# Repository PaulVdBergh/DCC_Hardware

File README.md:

# DCC_Hardware
The repository for DCC Hardware projects

The DCC project is an attempt to implement a DCC (Digital Command Control) Command Station based on the BeagleBone Black platform.
The project consists of four parts:
- DCC_BBB : the Linux code for the BeagleBone.
- DCC_PRU : the PRU code for generating the actuel DCC signal (including RailCom cutout).
- DCC_AVR : the AVR code for additional interfaces (for example Expressnet).
- DCC_Hardware (this repo) : the schematics and PCB-layout files for the hardware (KiCad)

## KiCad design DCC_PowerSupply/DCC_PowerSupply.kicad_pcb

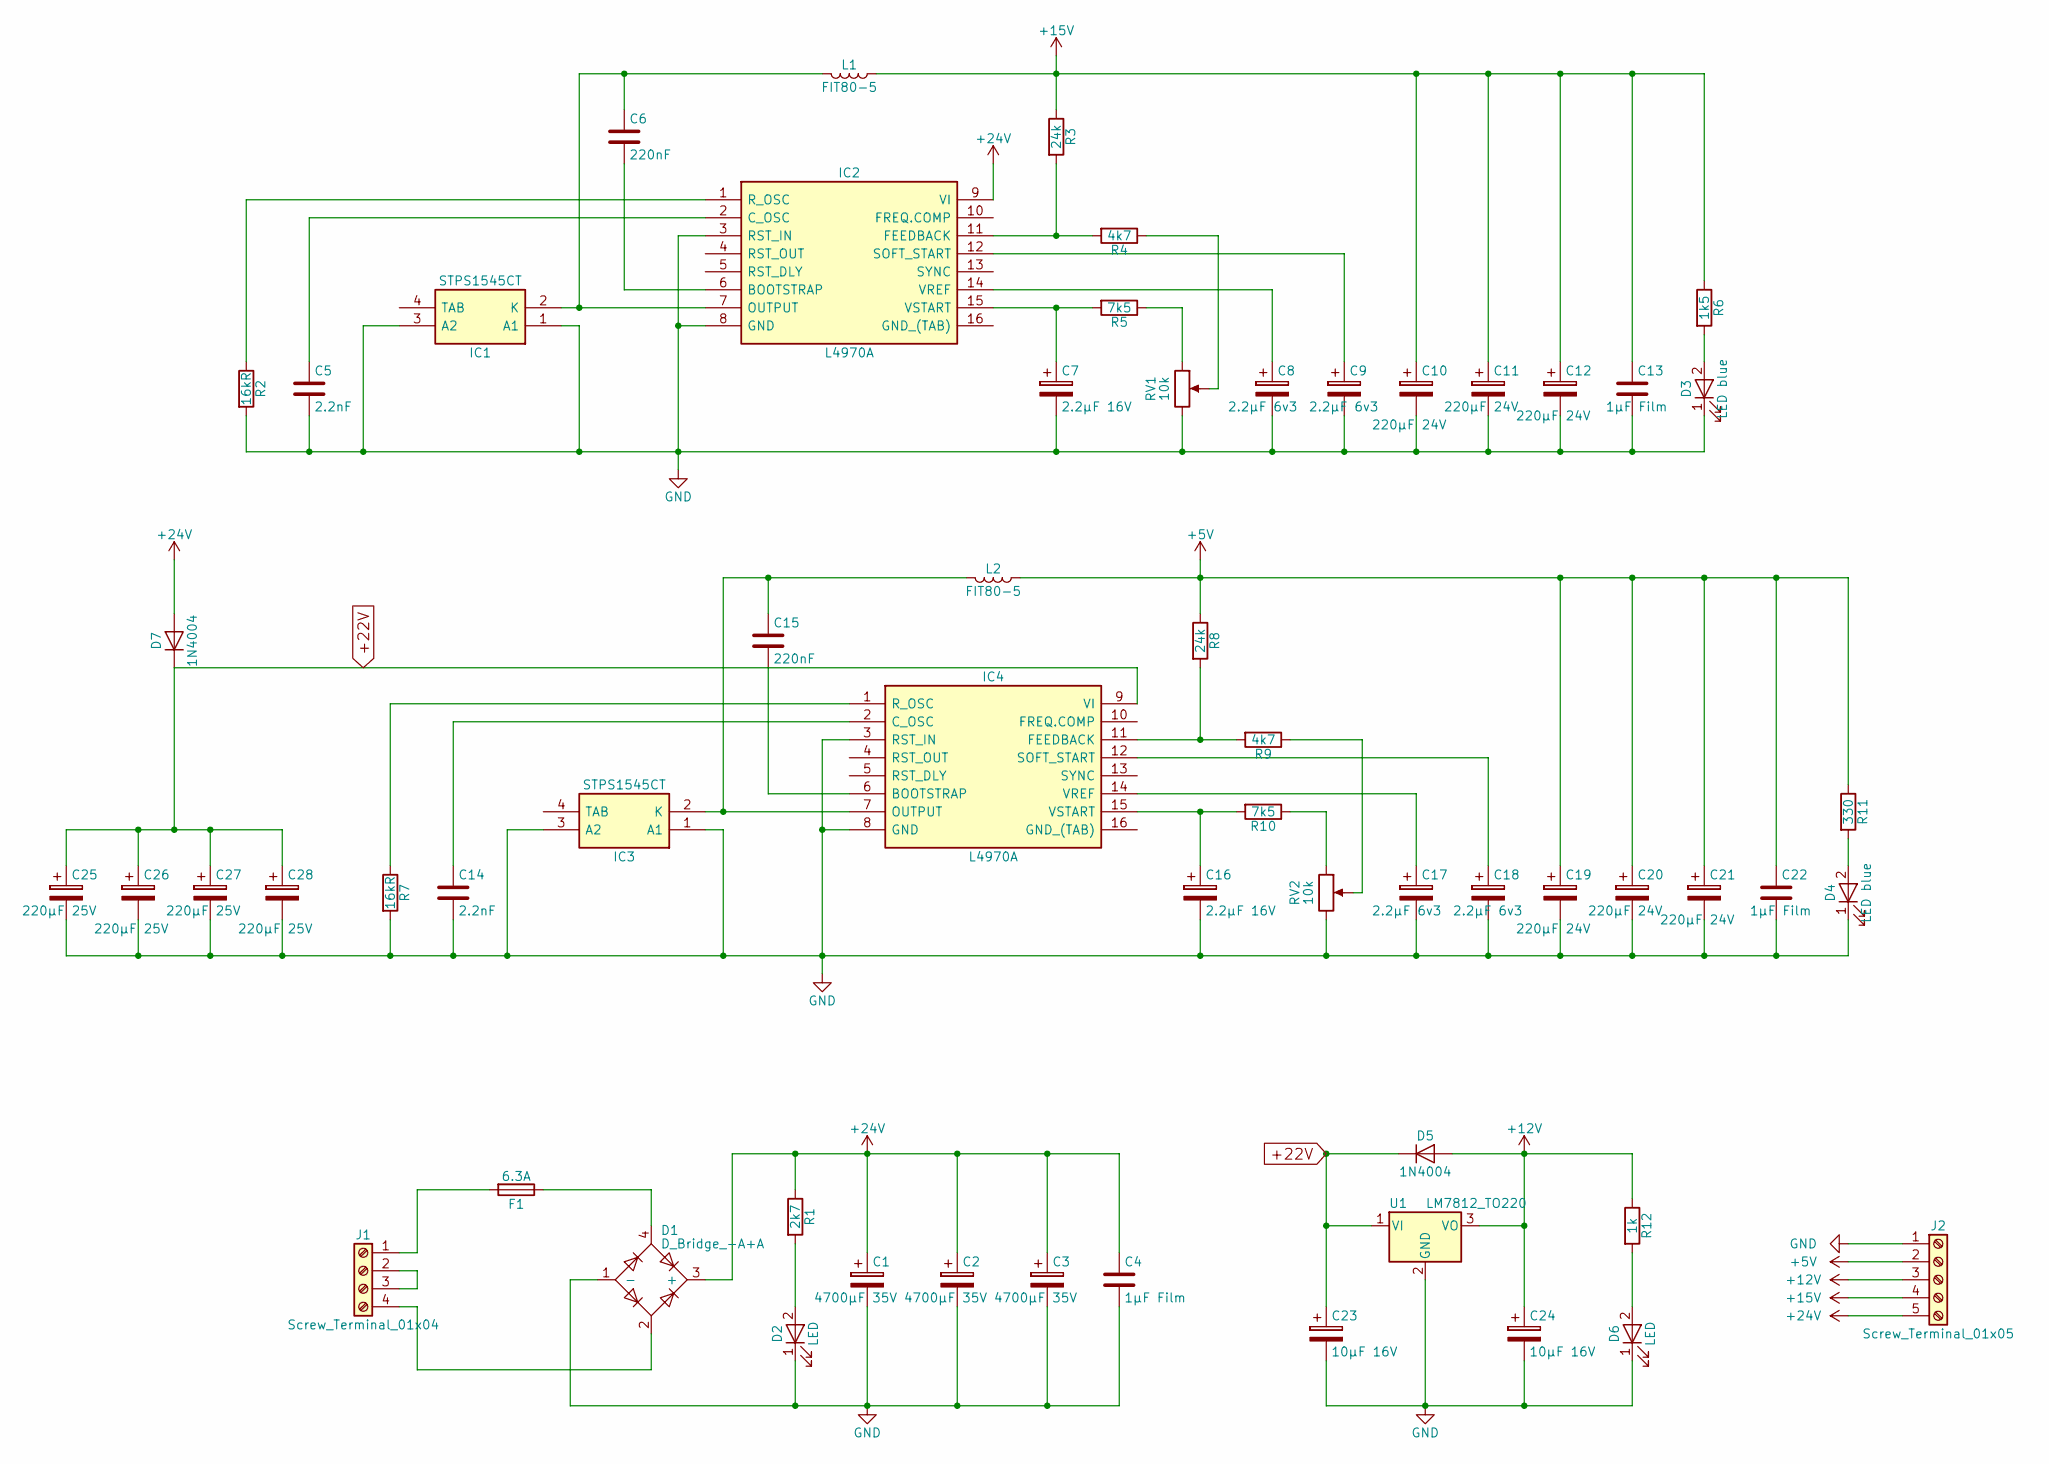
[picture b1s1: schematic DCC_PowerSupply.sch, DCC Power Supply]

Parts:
C1, C2, C3: 4700µF 35V; CP_Radial_D18.0mm_P7.50mm
C4, C13, C22: 1µF Film; C_Rect_L7.2mm_W7.2mm_P5.00mm_FKS2_FKP2_MKS2_MKP2
C5, C14: 2.2nF; C_Rect_L7.2mm_W2.5mm_P5.00mm_FKS2_FKP2_MKS2_MKP2
C6, C15: 220nF; C_Rect_L7.2mm_W2.5mm_P5.00mm_FKS2_FKP2_MKS2_MKP2
C7, C16: 2.2µF 16V; CP_Radial_D5.0mm_P2.00mm
C8, C9, C17, C18: 2.2µF 6v3; CP_Radial_D5.0mm_P2.00mm
C10, C11, C12, C19, C20, C21: 220µF 24V; CP_Radial_D8.0mm_P3.50mm
C23, C24: 10µF 16V; CP_Radial_D5.0mm_P2.00mm
C25, C26, C27, C28: 220µF 25V; CP_Radial_D8.0mm_P3.50mm
D1: D_Bridge_-A+A; Diode_Bridge_15.7x15.7
D2, D6: LED; LED_D3.0mm
D3, D4: LED blue; LED_D3.0mm
D5, D7: 1N4004; D_DO-41_SOD81_P7.62mm_Horizontal
F1: 6.3A; Fuseholder5x20_horiz_SemiClosed_Casing10x25mm
IC1, IC3: STPS1545CT; TO-220_Vertical; Manufacturer_Part_Number STPS1545CT
IC2, IC4: L4970A; Multiwatt-15_Vertical_StaggeredType1; Manufacturer_Part_Number L4970A
J1: Screw_Terminal_01x04; TerminalBlock_Philmore_TB13x_04x5mm_Straight
J2: Screw_Terminal_01x05; TerminalBlock_Philmore_TB13x_05x5mm_Straight
L1, L2: FIT80-5; L_Toroid_Vertical_L28.6mm_W14.3mm_P11.43mm_Bourns_5700
R1: 2k7; R_Axial_DIN0207_L6.3mm_D2.5mm_P10.16mm_Horizontal
R2, R7: 16kR; R_Axial_DIN0207_L6.3mm_D2.5mm_P10.16mm_Horizontal
R3, R8: 24k; R_Axial_DIN0207_L6.3mm_D2.5mm_P10.16mm_Horizontal
R4, R9: 4k7; R_Axial_DIN0207_L6.3mm_D2.5mm_P10.16mm_Horizontal
R5, R10: 7k5; R_Axial_DIN0207_L6.3mm_D2.5mm_P10.16mm_Horizontal
R6: 1k5; R_Axial_DIN0207_L6.3mm_D2.5mm_P10.16mm_Horizontal
R11: 330; R_Axial_DIN0207_L6.3mm_D2.5mm_P10.16mm_Horizontal
R12: 1k; R_Axial_DIN0207_L6.3mm_D2.5mm_P10.16mm_Horizontal
RV1, RV2: 10k; Potentiometer_Trimmer_Bourns_3339P_Horizontal
U1: LM7812_TO220; TO-220_Horizontal

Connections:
+5V: C19.1, C20.1, C21.1, C22.1, J2.2, L2.1, R8.1, R11.1
+12V: C24.1, D5.2 (A), J2.3, R12.1, U1.3 (VO)
+15V: C10.1, C11.1, C12.1, C13.1, J2.4, L1.1, R3.1, R6.1
+22V: C23.1, C25.1, C26.1, C27.1, C28.1, D5.1 (K), D7.1 (K), IC4.9 (VI), U1.1 (VI)
+24V: C1.1, C2.1, C3.1, C4.1, D1.3 (+), D7.2 (A), IC2.9 (VI), J2.5, R1.1
GND: C1.2, C2.2, C3.2, C4.2, C5.2, C7.2, C8.2, C9.2, C10.2, C11.2, C12.2, C13.2, C14.2, C16.2, C17.2, C18.2, C19.2, C20.2, C21.2, C22.2, C23.2, C24.2, C25.2, C26.2, C27.2, C28.2, D1.1 (-), D2.1 (K), D3.1 (K), D4.1 (K), D6.1 (K), IC1.1 (A1), IC1.3 (A2), IC2.3 (RST_IN), IC2.8 (GND), IC3.1 (A1), IC3.3 (A2), IC4.3 (RST_IN), IC4.8 (GND), J2.1, R2.2, R7.2, RV1.3, RV2.3, U1.2 (GND)
unnamed: C5.1, IC2.2 (C_OSC)
unnamed: C6.1, IC1.2 (K), IC2.7 (OUTPUT), L1.2
unnamed: C6.2, IC2.6 (BOOTSTRAP)
unnamed: C7.1, IC2.15 (VSTART), R5.2
unnamed: C8.1, IC2.14 (VREF)
unnamed: C9.1, IC2.12 (SOFT_START)
unnamed: C14.1, IC4.2 (C_OSC)
unnamed: C15.1, IC3.2 (K), IC4.7 (OUTPUT), L2.2
unnamed: C15.2, IC4.6 (BOOTSTRAP)
unnamed: C16.1, IC4.15 (VSTART), R10.2
unnamed: C17.1, IC4.14 (VREF)
unnamed: C18.1, IC4.12 (SOFT_START)
unnamed: D1.2, J1.4
unnamed: D1.4, F1.1
unnamed: D2.2 (A), R1.2
unnamed: D3.2 (A), R6.2
unnamed: D4.2 (A), R11.2
unnamed: D6.2 (A), R12.2
unnamed: F1.2, J1.1
unnamed: IC2.1 (R_OSC), R2.1
unnamed: IC2.11 (FEEDBACK), R3.2, R4.2
unnamed: IC4.1 (R_OSC), R7.1
unnamed: IC4.11 (FEEDBACK), R8.2, R9.2
unnamed: J1.2, J1.3
unnamed: R4.1, RV1.2
unnamed: R5.1, RV1.1
unnamed: R9.1, RV2.2
unnamed: R10.1, RV2.1

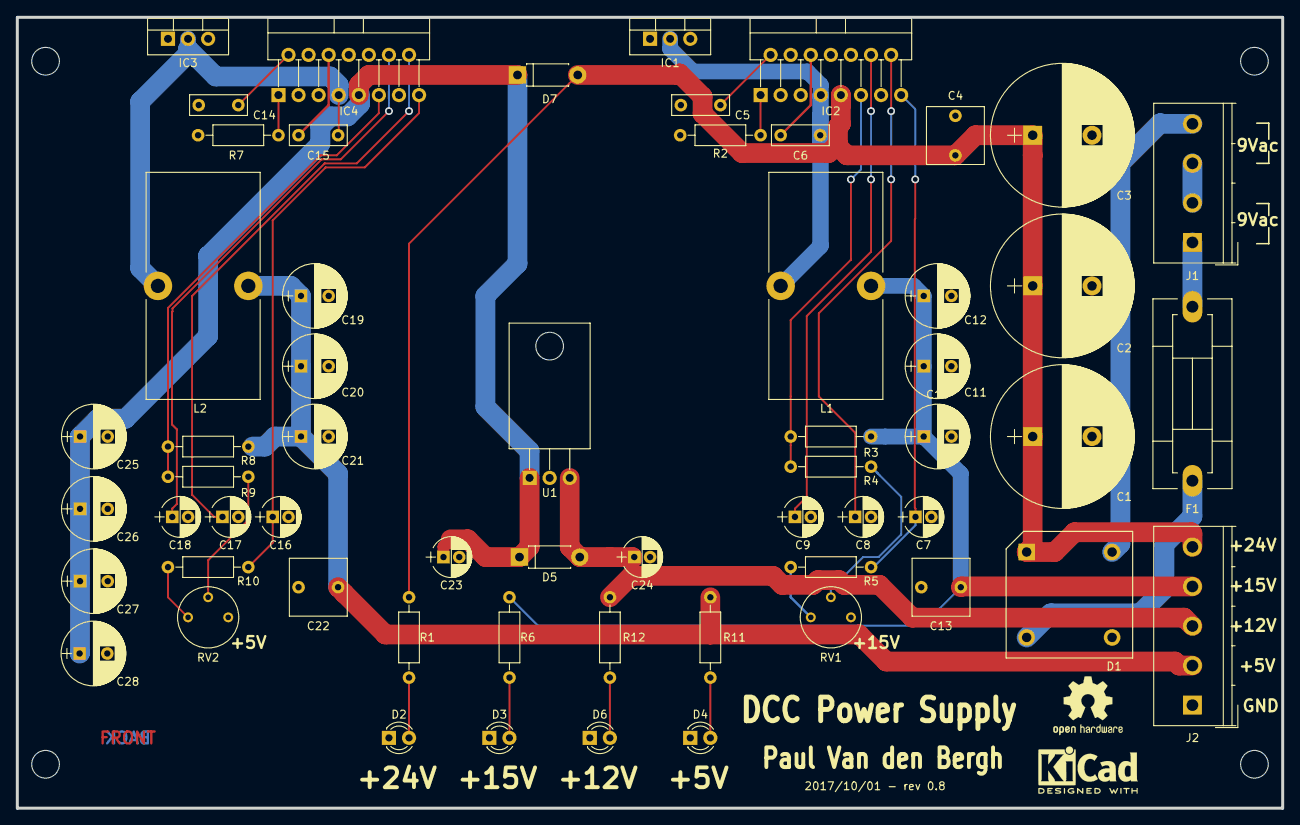
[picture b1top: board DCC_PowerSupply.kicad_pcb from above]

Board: 2 copper layers, 160.0 x 100.0 mm, 60 parts (0 on the bottom side), 34 nets.

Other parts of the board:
2017/10/01 - rev 0.8: EuroBoard160mmX100mm_holes

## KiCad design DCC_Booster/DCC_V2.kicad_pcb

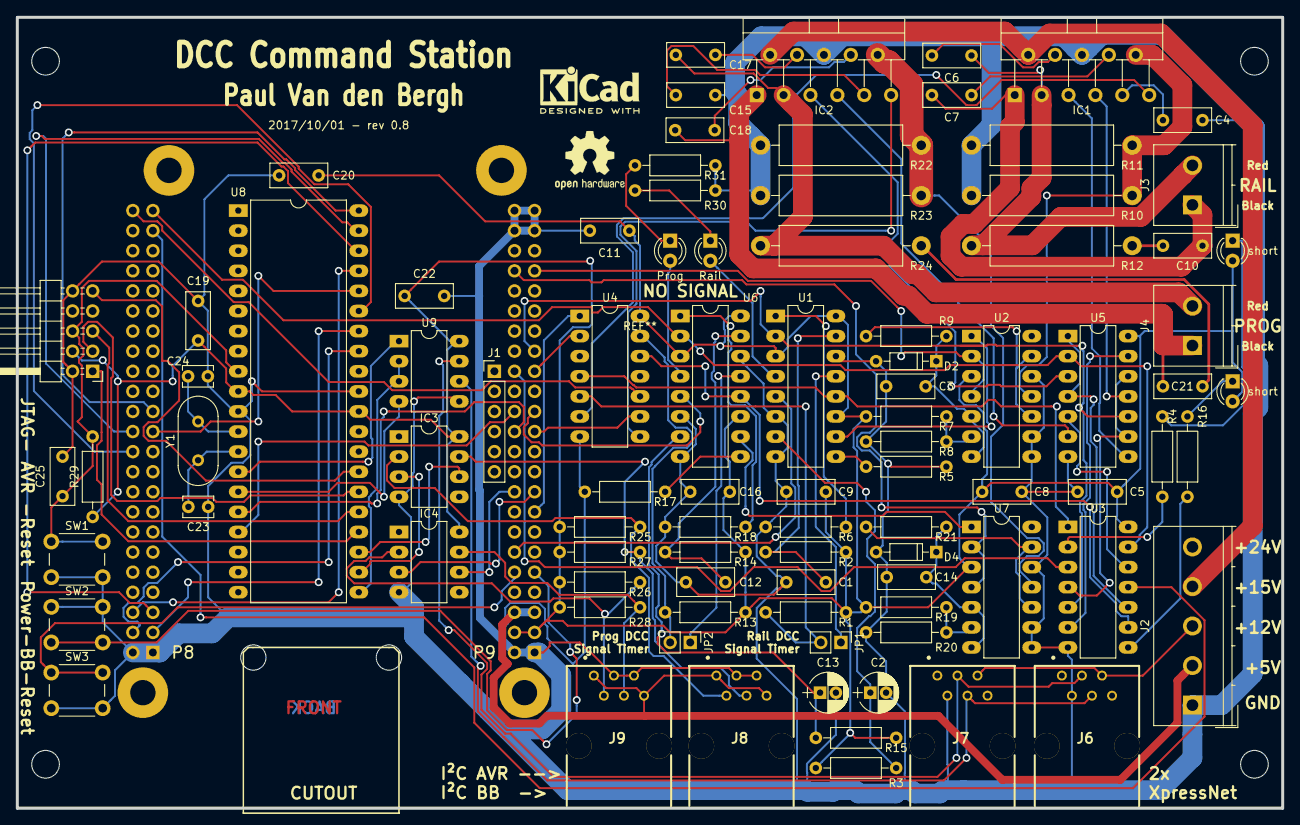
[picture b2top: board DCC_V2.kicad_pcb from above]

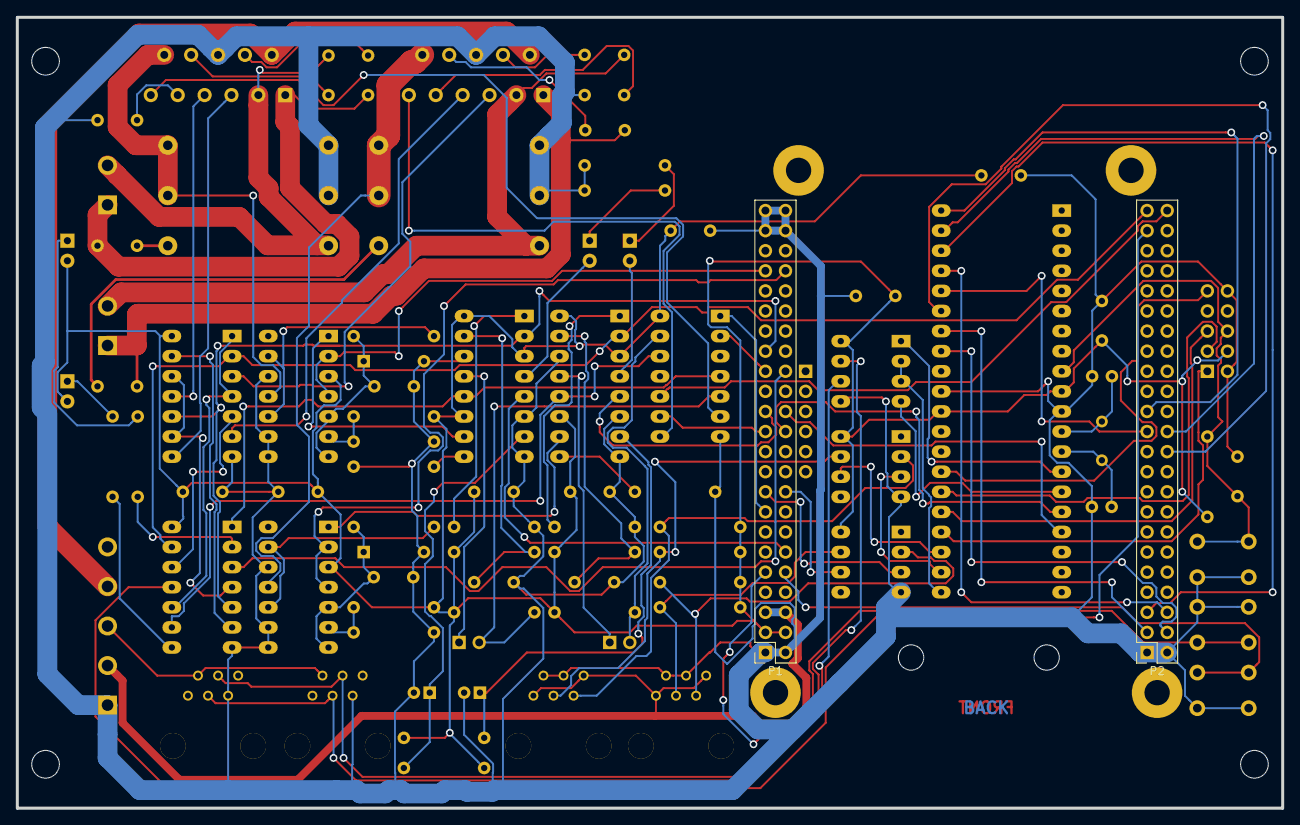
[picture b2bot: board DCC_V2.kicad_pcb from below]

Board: 2 copper layers, 160.0 x 100.0 mm, 94 parts (2 on the bottom side), 103 nets.

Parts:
AVR JTAG: Conn_02x05_Odd_Even; Pin_Header_Angled_2x05_Pitch2.54mm
C1, C5, C8, C9, C10, C11, C16, C19, C20, C21, C22, C25: 100nF; C_Rect_L7.2mm_W3.0mm_P5.00mm_FKS2_FKP2_MKS2_MKP2
C2: 10µF 6.3V; CP_Radial_D5.0mm_P2.00mm
C3, C14: 10nF; C_Rect_L7.2mm_W3.0mm_P5.00mm_FKS2_FKP2_MKS2_MKP2
C4, C15: 220nF; C_Rect_L7.2mm_W3.0mm_P5.00mm_FKS2_FKP2_MKS2_MKP2
C6, C7, C17, C18: 15nF; C_Rect_L7.2mm_W3.0mm_P5.00mm_FKS2_FKP2_MKS2_MKP2
C12: 100nF; C_Rect_L7.2mm_W3.5mm_P5.00mm_FKS2_FKP2_MKS2_MKP2
C13: 10µF; CP_Radial_D5.0mm_P2.00mm
C23, C24: 22pF; C_Disc_D3.8mm_W2.6mm_P2.50mm
D2, D4: 1N4614; D_DO-35_SOD27_P7.62mm_Horizontal
IC1, IC2: L6203; Multiwatt-11_Vertical_StaggeredType1
IC3, IC4: P82B715PN; DIP-8_W7.62mm_LongPads
J1: Conn_01x06_Female; Socket_Strip_Straight_1x06_Pitch2.54mm
J2: Screw_Terminal_01x05; TerminalBlock_Philmore_TB13x_05x5mm_Straight
J3, J4: Screw_Terminal_01x02; TerminalBlock_Philmore_TB132_02x5mm_Straight
J6, J7, J8, J9: 54601-906WPLF
JP1, JP2: Jumper; Pin_Header_Straight_1x02_Pitch2.54mm
P1: BBB_P9; Socket_Strip_Straight_2x23_Pitch2.54mm
P2: BBB_P8; Socket_Strip_Straight_2x23_Pitch2.54mm
P8, P9: MountingHole_3.2mm_M3_Pad
Prog: LED; LED_D3.0mm
R1, R5, R6, R13, R17, R18: 4k7; R_Axial_DIN0207_L6.3mm_D2.5mm_P10.16mm_Horizontal
R2, R3, R14, R15: 33k; R_Axial_DIN0207_L6.3mm_D2.5mm_P10.16mm_Horizontal
R4, R16: R; R_Axial_DIN0207_L6.3mm_D2.5mm_P10.16mm_Horizontal
R7: 12k; R_Axial_DIN0207_L6.3mm_D2.5mm_P10.16mm_Horizontal
R8, R9, R20, R21, R29: 10k; R_Axial_DIN0207_L6.3mm_D2.5mm_P10.16mm_Horizontal
R10, R11, R22, R23: 0.5 2W; R_Axial_DIN0516_L15.5mm_D5.0mm_P20.32mm_Horizontal
R12, R24: 100 2W; R_Axial_DIN0516_L15.5mm_D5.0mm_P20.32mm_Horizontal
R19: 78k; R_Axial_DIN0207_L6.3mm_D2.5mm_P10.16mm_Horizontal
R25, R26, R27, R28: 270; R_Axial_DIN0207_L6.3mm_D2.5mm_P10.16mm_Horizontal
R30, R31: 330; R_Axial_DIN0207_L6.3mm_D2.5mm_P10.16mm_Horizontal
Rail: LED; LED_D3.0mm
SW1: SW_DPST; SW_PUSH_6mm
SW2: Power; SW_PUSH_6mm
SW3: Reset; SW_PUSH_6mm
U1, U6: 74HC123; DIP-16_W7.62mm_LongPads
U2, U7: LM339; DIP-14_W7.62mm_LongPads
U3: 74HC04; DIP-14_W7.62mm_LongPads
U4: 74HC21; DIP-14_W7.62mm_LongPads
U5: 74HC08; DIP-14_W7.62mm_LongPads
U8: ATMEGA1284-PU; DIP-40_W15.24mm_LongPads
U9: MAX485E; DIP-8_W7.62mm_LongPads
Y1: 16MHz; Crystal_HC18-U_Vertical
short: LED; LED_D3.0mm
short#2: LED; LED_D3.0mm

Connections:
+3V3: AVR JTAG.4, C5.1, C8.1, C9.1, C11.1, C16.1, C19.1, C20.1, C22.1, IC3.8, IC4.8, P1.3, P1.4, R1.1, R2.1, R3.1, R7.1, R13.1, R14.1, R15.1, R19.1, R25.1, R26.1, R27.1, R28.1, R29.1, U1.3, U1.11, U1.16, U2.3, U3.14, U4.14, U5.14, U6.3, U6.11, U6.16, U7.3, U8.10, U8.30, U9.8, short.2, short#2.2
+5V: J2.2, J8.1, J8.6, J9.1, J9.6, P1.5, P1.6
+12V: J2.3, J6.5, J7.5
+15V: IC1.2, IC2.2, J2.4
GND: AVR JTAG.2, AVR JTAG.10, C1.2, C2.2, C3.2, C4.2, C5.2, C8.2, C9.2, C11.2, C12.2, C13.2, C14.2, C15.2, C16.2, C19.2, C20.2, C22.2, C23.2, C24.1, C25.2, D2.2, D4.2, IC1.6, IC2.6, IC3.4, IC4.4, J2.1, J6.2, J7.2, J8.3, J8.5, J9.3, J9.5, P1.1, P1.2, P1.43, P1.44, P1.45, P1.46, P2.1, P2.2, R5.2, R6.2, R8.2, R10.2, R11.2, R17.2, R18.2, R20.2, R22.2, R23.2, R30.2, R31.2, SW1.2, SW2.1, SW3.2, U1.6, U1.8, U1.14, U2.8, U2.9, U2.12, U3.7, U4.7, U5.7, U6.6, U6.8, U6.14, U7.8, U7.9, U7.12, U8.11, U8.31, U9.5
GPIO1_0: P2.25, U8.40
GPIO1_1: P2.24, U8.39
GPIO1_2: P2.5, U8.38
GPIO1_3: P2.6, U8.37
GPIO1_4: P2.23, U8.36
GPIO1_5: P2.22, U8.35
GPIO1_6: P2.3, U8.34
GPIO1_7: P2.4, U8.33
I2C1_SCL: IC4.3, P1.17
I2C1_SDA: IC4.6, P1.18
Linux_Analog_Current: P1.39, U2.2, U2.4
Linux_OverCurrent: P1.12, U1.5
Linux_Prog_Analog_Current: P1.40, U7.2, U7.4
Linux_Prog_OverCurrent: P1.25, U6.5
Linux_Prog_RailPower: P1.23, U4.9
Linux_RailPower: P1.15, U4.1
unnamed: C1.1, R2.2, U1.15
unnamed: C2.1, R3.2, U1.7
unnamed: C3.1, D2.1, R9.2, U2.5, U2.7
unnamed: C4.1, IC1.9
unnamed: C6.2, IC1.4
unnamed: C7.1, IC1.8
unnamed: C10.1, R12.2
unnamed: C12.1, R14.2, U6.15
unnamed: C13.1, R15.2, U6.7
unnamed: C14.1, D4.1, R21.2, U7.5, U7.7
unnamed: C15.1, IC2.9
unnamed: C17.2, IC2.4
unnamed: C18.1, IC2.8
unnamed: C21.1, R24.2
unnamed: C23.1, U8.13, Y1.1
unnamed: C24.2, U8.12, Y1.2
unnamed: AVR JTAG.6, C25.1, R29.2, SW1.1, U8.9
unnamed: R4.1, short.1
unnamed: R16.1, short#2.1
unnamed: R30.1, Rail.1
unnamed: Rail.2, U1.4
unnamed: Prog.1, R31.1
unnamed: Prog.2, U6.4
unnamed: IC1.5, U5.8
unnamed: IC1.7, U5.11
unnamed: IC1.10, R10.1, R11.1, U2.11
unnamed: IC1.11, U4.6
unnamed: IC2.5, U5.3
unnamed: IC2.7, U5.6
unnamed: IC2.10, R22.1, R23.1, U7.11
unnamed: IC2.11, U4.8
unnamed: IC3.2, J8.2, R25.2
unnamed: IC3.3, U8.22
unnamed: IC3.6, U8.23
unnamed: IC3.7, J8.4, R27.2
unnamed: IC4.2, J9.2, R26.2
unnamed: IC4.7, J9.4, R28.2
unnamed: AVR JTAG.1, U8.24
unnamed: AVR JTAG.3, U8.26
unnamed: AVR JTAG.5, U8.25
unnamed: AVR JTAG.9, U8.27
unnamed: J6.3, J7.3, U9.7
unnamed: J6.4, J7.4, U9.6
unnamed: JP1.1, U1.13
unnamed: JP1.2, R1.2, U4.5
unnamed: JP2.1, U6.13
unnamed: JP2.2, R13.2, U4.13
unnamed: P1.9, SW2.2
unnamed: P1.10, SW3.1
unnamed: R4.2, U3.2
unnamed: R5.1, U1.9
unnamed: R6.1, U1.1
unnamed: R7.2, R8.1, U2.6
unnamed: R9.1, U2.10, U2.13
unnamed: R16.2, U3.8
unnamed: R17.1, U6.9
unnamed: R18.1, U6.1
unnamed: R19.2, R20.1, U7.6
unnamed: R21.1, U7.10, U7.13
unnamed: U1.10, U2.1
unnamed: U1.12, U3.1, U4.4
unnamed: U3.4, U5.9, U5.12
unnamed: U3.6, U5.13
unnamed: U3.9, U4.12, U6.12
unnamed: U3.10, U5.1, U5.4
unnamed: U3.12, U5.5
unnamed: U6.10, U7.1
unnamed: U8.14, U9.1
unnamed: U8.15, U9.4
unnamed: U8.21, U9.2, U9.3
PRUSS_DCC: P1.31, U1.2, U3.5, U5.10
PRUSS_Prog_DCC: P2.45, U3.13, U5.2, U6.2
PRUSS_Prog_RailPower: P2.46, U4.10
PRUSS_Prog_RailcomGap: P2.43, U3.11
PRUSS_RailPower: P1.29, U4.2
PRUSS_RailcomGap: P1.30, U3.3
Prog_Rail_Black: C18.2, C21.2, IC2.1, J4.1
Prog_Rail_Red: C17.1, IC2.3, J4.2, R24.1
Rail_Black: C7.2, C10.2, IC1.1, J3.1
Rail_Red: C6.1, IC1.3, J3.2, R12.1
UART1_RXD: P1.26, U8.17
UART1_TXD: P1.24, U8.16

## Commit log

2017-10-30 initial

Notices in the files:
DCC_PowerSupply/DCC_PowerSupply.sch:
(c) 2017 - Paul Van den Bergh
